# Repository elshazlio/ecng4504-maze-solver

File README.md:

# ECNG 4504 — Autonomous maze-learning & maze-solving robot

**American University in Cairo · School of Sciences and Engineering**  
**ECNG 4504 — Embedded Systems for Wireless Communications · Spring 2026**

---

## Abstract

This project is an **autonomous line-following robot** that **learns** an unknown maze in a training pass and later **executes a shortened turn sequence** to reach the goal efficiently. A **PC host** connects over **Bluetooth** (BLE with HM-10, or **Bluetooth Classic SPP** with a ZS-040 / HC-05) to issue commands, stream status, and visualize behavior. On-robot software is a single Arduino sketch (`working_code.ino`) built around **discrete line following** (no PID), **left-hand-rule** decisions at intersections, **in-place path simplification**, and **EEPROM** persistence of the optimized path.

---

## How we approached the project

We treated the work as a loop of **measure → interpret → act → log**, repeated until the vehicle behaved reliably on real tape and real junction geometry.

1. **Hardware and sensing**  
   We brought up **five reflective sensors** (left-to-right array), **differential drive** via motor drivers, and **wireless UART on `Serial1`** (HM-10 BLE or ZS-040 / HC-05 classic) so the laptop could see the same telemetry as USB debug.

2. **Baseline motion**  
   Before worrying about mapping, we stabilized **line following** using **fixed PWM steps** and simple rules from the sensor pattern (centered forward, soft correct near center, stronger correct when the line moves under an outer sensor). This deliberately avoids PID tuning loops in favor of predictable, repeatable motion on our course.

3. **Seeing intersections**  
   Real junctions rarely match ideal drawings: wide tape, gaps, and noise meant “all black” or “wide center” could mean different things. We added **timing and lockouts** (`NODE_LOCKOUT_MS`) so the robot did not re-trigger the same junction, and **short probe moves** with **burst sampling** across the array to classify **left / straight / right** exits when possible.

4. **Training as a path string**  
   During **training**, at each real decision node the robot applies the **left-hand rule**: prefer **L**, then **S**, then **R**. The sequence of taken turns is appended to a **raw path** (`L`, `S`, `R`, or `B` for dead-end / U-turn). **Dead ends** are detected when the line is lost for long enough and recovered with a **U-turn** and a recorded **`B`**.

5. **When geometry is ambiguous**  
   For **multi-exit** junctions, recording is **deferred** briefly: after the turn, the firmware **accumulates “witness”** from the outer sensors and **scores candidate exit masks** so the stored junction record matches what the robot actually saw after committing to a turn.

6. **Optimizing the remembered path**  
   After training, the firmware **folds** the raw path: any **middle `B`** (dead-end) with neighbors is combined using **turn angles** (90° increments) so backtracking detours collapse into a single equivalent turn. That yields the **optimal path** string used in solve mode.

7. **Solve mode**  
   In **solving**, the robot walks the **optimized** sequence: at each true decision node it executes the next character of `optimalPath`. If sensor classification and the stored path disagree, it logs a **mismatch** and falls back to the left-hand choice so the run degrades safely.

8. **Host software**  
   We built a **FastAPI** dashboard with **WebSockets** (`Bluetooth stuff/maze_dashboard/`) — **Bleak** for BLE, or **pyserial** to a paired **Bluetooth SPP** serial port on macOS — plus a small **Bun** log viewer (`Bluetooth stuff/log-viewer/`) to command `TRAIN` / `START`, watch logs, and debug link issues.

**Diagrams in this repo:** high-level software structure is in [`system_architecture.png`](system_architecture.png); the PCB is exported as [`PCB Schematic.png`](PCB Schematic.png). Team and roles are in [`team.md`](team.md).

---

## Firmware: theory and implementation

The firmware implements a **maze-learning** pipeline that is **graph-free** on the MCU: the map is a **string of turns**, not an explicit adjacency list. That matches the course emphasis on embedded constraints and clear state machines.

### Line following without PID

Line tracking uses **rule-based steering** (`followLineNoPID`): the center sensor defines “on track,” left/right pairs request **differential spins** at tuned speeds (`BASE_SPEED`, `TURN_SPEED`, `ALIGN_SPEED`, etc.). There is **no PID controller**—the design trades fine continuous control for **bounded behavior** that is easier to reason about on inconsistent surfaces. After turns, **`alignToCenterStrict`** recenters on a **center-only** pattern before moving forward.

### Junction detection and training probes

A **node candidate** is inferred from reflective patterns (`nodeCandidateNow`): e.g. **all sensors on line** (wide intersection) or **outer sensors with inner body**. After a lockout window, the robot stops and runs **`inspectAndHandleNodeTraining`**: short forward motion **samples bursts** of left/right/straight visibility to set **exit masks** (bits for L, S, R). The **left-hand rule** (`selectTurn`) chooses the physical turn. **Finish** is a sustained **all-black** region confirmed as the end box (`confirmEndBox`).

### Recording and deferred resolution

For junctions with **multiple** plausible exits, the firmware may **defer** committing the recorded mask (`finalizePendingTrainingRecord`, `RECORD_RESOLVE_MS`) so post-turn sensor **witnesses** improve which mask is stored with the segment time. **Single-exit** corridors force a turn without the same ambiguity.

### Path optimization (dead-end folding)

The **raw** training path includes detours. **`buildOptimalPath`** repeatedly replaces triples where the **middle turn is `B`** by summing **turn angles** (L = 270°, S = 0°, R = 90°, B = 180°) and mapping the result back to a single letter. This removes redundant **out-and-back** structure while preserving net heading.

### Solving

**Solve** mode (`inspectAndHandleNodeSolving`) indexes **`optimalPath`** with `solveStepIndex`. Only at **true** decision nodes (multiple exits, or zero exits) does it consume the next stored turn; **forced** corridors follow the obvious exit. EEPROM (`EepromMazeData`) can persist raw and optimized paths across power cycles (`LOAD`, `CLEAR`, auto-load on boot).

### Commands and telemetry

**USB and wireless UART** share the same command set (`TRAIN`, `START`/`SOLVE`, `STATUS`, `DUMP`, `LOAD`, `CLEAR`, `STOP`). Status lines (`STATE`, `STAGE`, paths, node logs) go to both streams for the dashboard and debugging.

---

## Repository contents

| Deliverable | Location |
|-------------|----------|
| MCU firmware (final) | [`working_code.ino`](working_code.ino) |
| Backend (FastAPI, BLE, WebSockets) | [`Bluetooth stuff/maze_dashboard/`](Bluetooth%20stuff/maze_dashboard/) |
| Web UI (log viewer) | [`Bluetooth stuff/log-viewer/`](Bluetooth%20stuff/log-viewer/) |
| BLE helper scripts | [`Bluetooth stuff/ble_log_receiver.py`](Bluetooth%20stuff/ble_log_receiver.py), [`Bluetooth stuff/ble_scan.py`](Bluetooth%20stuff/ble_scan.py), [`Bluetooth stuff/requirements.txt`](Bluetooth%20stuff/requirements.txt) |
| Bill of materials | [`component_list(1).xlsx`](component_list%281%29.xlsx) |
| Software architecture diagram | [`system_architecture.png`](system_architecture.png) |
| PCB schematic (image export) | [`PCB Schematic.png`](PCB%20Schematic.png) (also under [`KiCAD Stuff/`](KiCAD%20Stuff/)) |
| KiCAD project (native) | [`KiCAD Stuff/`](KiCAD%20Stuff/) — `Embedded Project.kicad_pro`, `.kicad_sch`, `.kicad_pcb`, `.kicad_prl` |
| Team | [`team.md`](team.md) |
| 3D / mechanical design | [`3d design/`](3d%20design/) (Fusion 360 `.f3z`) |
| Local dev (env + both servers) | [`DEV-SERVERS.md`](DEV-SERVERS.md) |

**KiCAD:** open **`KiCAD Stuff/Embedded Project.kicad_pro`** in **KiCad**. Local editor folders (`.history/`, `*-backups/`, lock files) are gitignored.

---

## Running the PC applications

The host uses the **same UART protocol** as USB; the **radio path** is either **Bluetooth Classic SPP** (ZS-040 / HC-05) or **BLE** (HM-10 / Nordic UART). Full copy-paste flows (both apps, stop commands, ports) are in **[`DEV-SERVERS.md`](DEV-SERVERS.md)**.

- **Classic SPP (`ZS-040 / HC-05`):** pair in macOS, then set `MAZE_BT_SERIAL` to the paired `/dev/cu.*` device (and `MAZE_BT_BAUD`, usually `9600`). Applies to **both** the maze dashboard and the log viewer.
- **BLE:** leave `MAZE_BT_SERIAL` unset. Point the **dashboard** at the robot with `MAZE_BLE_ADDR` (fixed address, skips scanning) or `MAZE_BLE_NAME` (scan by advertised name). The **log viewer** does **not** use `MAZE_BLE_ADDR`; it still expects `MAZE_BT_SERIAL` for Classic SPP.

**Maze dashboard (first-time venv)**

```bash
cd "Bluetooth stuff/maze_dashboard"
python3 -m venv .venv && source .venv/bin/activate && pip install -r requirements.txt
uvicorn app:app --reload --host 127.0.0.1 --port 8765
```

**ZS-040 / HC-05 on macOS (Bluetooth Classic SPP)** — pair the module in **System Settings → Bluetooth**, then pick the outgoing serial device (names vary; often under `/dev/cu.*`):

```bash
ls /dev/cu.*
export MAZE_BT_SERIAL=/dev/cu.YourModule-DevB
export MAZE_BT_BAUD=9600
cd "Bluetooth stuff/maze_dashboard"
source .venv/bin/activate
uvicorn app:app --reload --host 127.0.0.1 --port 8765
```

After a successful connection, you can use `export MAZE_BT_SERIAL=last` to reuse `bt_serial_last.json` beside `app.py`.

**Maze dashboard (BLE by address — example)**

Use when the robot is on the BLE path and you already know its address:

```bash
unset MAZE_BT_SERIAL
unset MAZE_BT_BAUD
export MAZE_BLE_ADDR=78:04:73:16:19:C7
cd "Bluetooth stuff/maze_dashboard"
source .venv/bin/activate
uvicorn app:app --reload --host 127.0.0.1 --port 8765
```

For scan-based BLE instead of a fixed address, omit `MAZE_BLE_ADDR` and optionally set `MAZE_BLE_NAME`. See `Bluetooth stuff/maze_dashboard/app.py` (module docstring) and `ble_discover.py` for UUID discovery.

**Path preview (SVG map):** The dashboard builds a **turtle-geometry** polyline from path strings and from **training/solve** turn lines in the log (`FORCED_TURN`, `SOLVE_FORCED_TURN`, `SOLVE_NODE`, etc.). The preview appends **one grid segment after the last logged turn** so the **final leg** and **forced** corridor exits show the same corners you see on the track; that step is **visualization-only** and does not change what the robot records or executes. Optional **local-only** regression tests for the map (not published on GitHub) may exist under `Bluetooth stuff/maze_dashboard/`; if you have them, run with `python -m unittest` in that folder using the project venv.

**Log viewer** (see `Bluetooth stuff/log-viewer/package.json` for scripts). This path uses `ble_log_receiver.py` and **Classic SPP only** — set `MAZE_BT_SERIAL` in the same shell.

```bash
cd "Bluetooth stuff/log-viewer"
bun install
export MAZE_BT_SERIAL=/dev/cu.YourModule-DevB
bun run serve
```

---

*Course project repository: **ecng4504-maze-solver_team_5** — maze learning and solving per the ECNG 4504 charter.*

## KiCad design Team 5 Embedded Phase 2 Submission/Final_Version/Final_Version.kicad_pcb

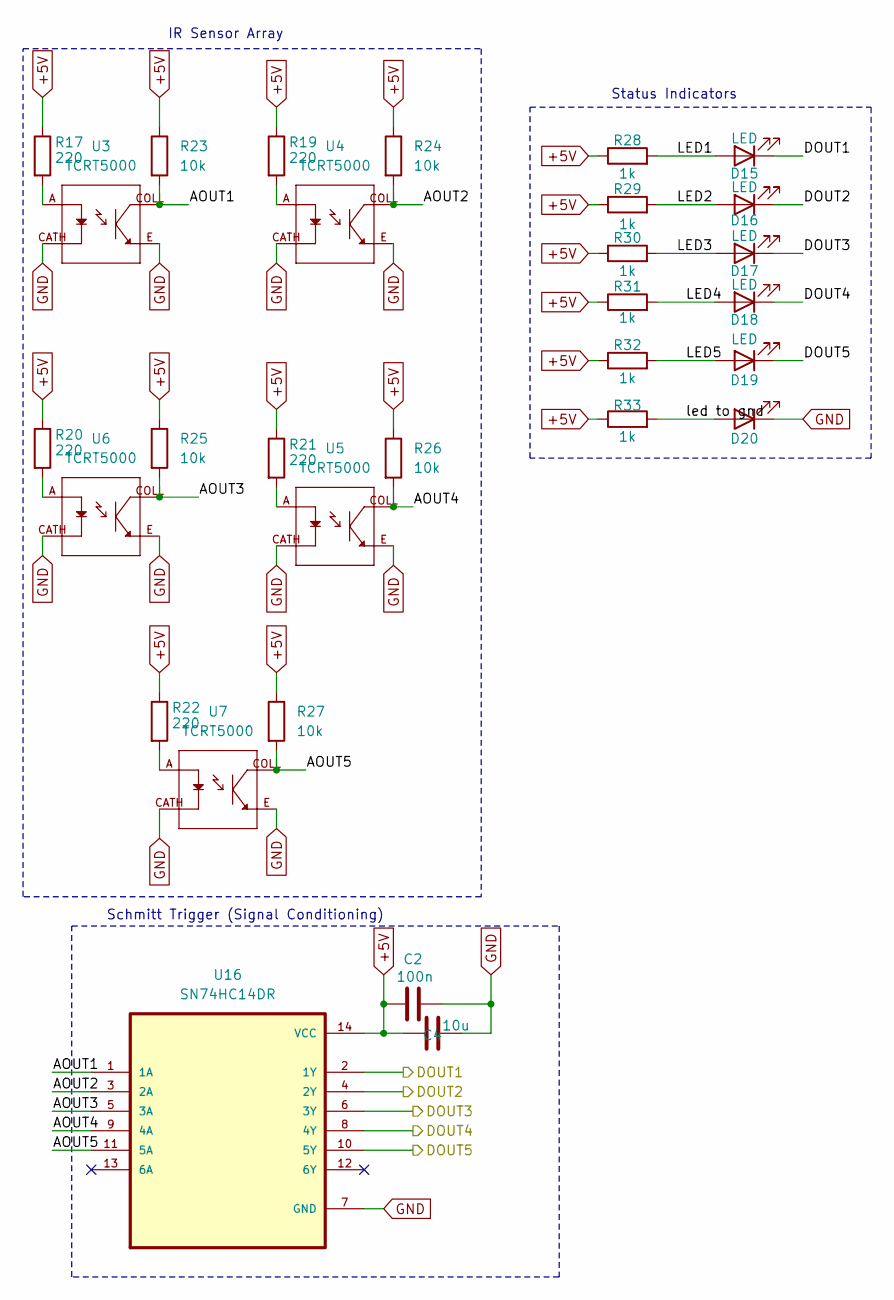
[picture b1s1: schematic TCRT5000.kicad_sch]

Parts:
C2: 100n; C_0805_2012Metric
C4: 10u; C_0805_2012Metric
D15, D16, D17, D18, D19, D20: LED; LED_0805_2012Metric
R17, R19, R20, R21, R22: 220; R_0805_2012Metric
R23, R24, R25, R26, R27: 10k; R_0805_2012Metric
R28, R29, R30, R31, R32, R33: 1k; R_0805_2012Metric
U3, U4, U5, U6, U7: TCRT5000; OPTO_TCRT5000; PARTREV 1.7
U16: SN74HC14DR; SOIC127P600X175-14N

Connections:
+5V: C2.1, C4.1, R17.1, R19.1, R20.1, R21.1, R22.1, R23.1, R24.1, R25.1, R26.1, R27.1, R28.1, R29.1, R30.1, R31.1, R32.1, R33.1, U16.14 (VCC); also elsewhere on the board
/TCRT5000/AOUT1: R23.2, U3.COLL, U16.1 (1A)
/TCRT5000/AOUT2: R24.2, U4.COLL, U16.3 (2A)
/TCRT5000/AOUT3: R25.2, U6.COLL, U16.5 (3A)
/TCRT5000/AOUT4: R26.2, U5.COLL, U16.9 (4A)
/TCRT5000/AOUT5: R27.2, U7.COLL, U16.11 (5A)
/TCRT5000/DOUT1: D15.1 (K), U16.2 (1Y); also elsewhere on the board
/TCRT5000/DOUT2: D16.1 (K), U16.4 (2Y); also elsewhere on the board
/TCRT5000/DOUT3: D17.1 (K), U16.6 (3Y); also elsewhere on the board
/TCRT5000/DOUT4: D18.1 (K), U16.8 (4Y); also elsewhere on the board
/TCRT5000/DOUT5: D19.1 (K), U16.10 (5Y); also elsewhere on the board
/TCRT5000/LED1: D15.2 (A), R28.2
/TCRT5000/LED2: D16.2 (A), R29.2
/TCRT5000/LED3: D17.2 (A), R30.2
/TCRT5000/LED4: D18.2 (A), R31.2
/TCRT5000/LED5: D19.2 (A), R32.2
/TCRT5000/led to gnd: D20.2 (A), R33.2
GND: C2.2, C4.2, D20.1 (K), U3.CATH, U3.E, U4.CATH, U4.E, U5.CATH, U5.E, U6.CATH, U6.E, U7.CATH, U7.E, U16.7 (GND); also elsewhere on the board
unnamed: R17.2, U3.A
unnamed: R19.2, U4.A
unnamed: R20.2, U6.A
unnamed: R21.2, U5.A
unnamed: R22.2, U7.A

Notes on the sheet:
IR Sensor Array
Status Indicators
Schmitt Trigger (Signal Conditioning)

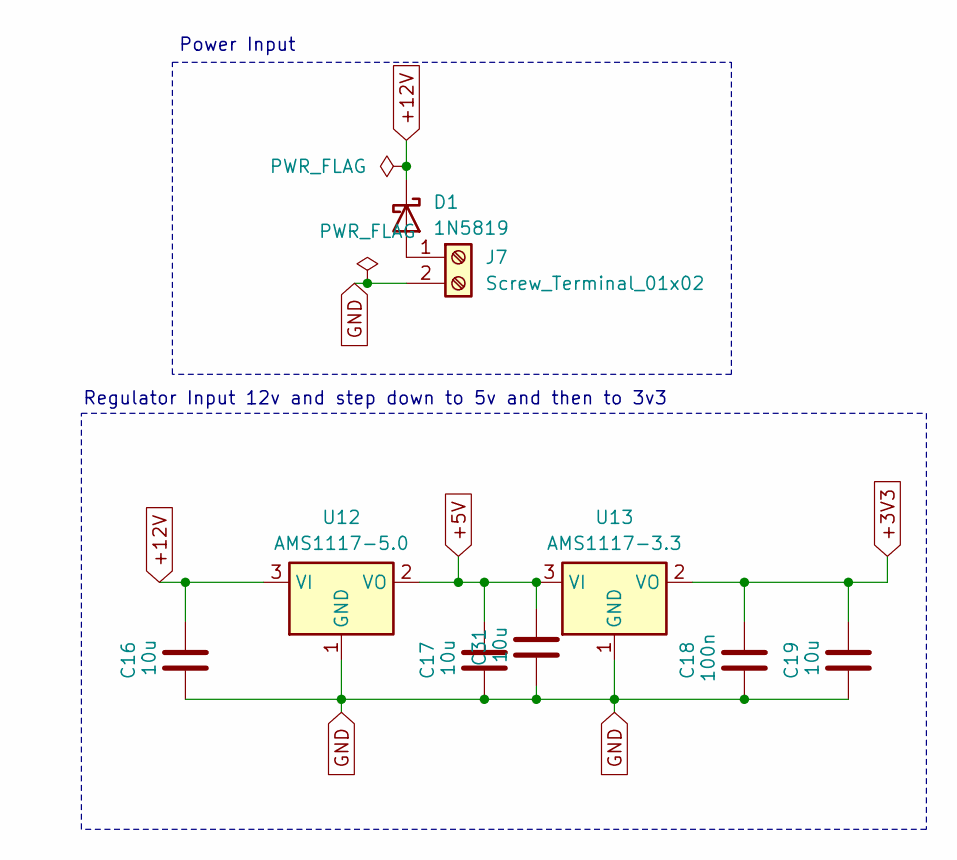
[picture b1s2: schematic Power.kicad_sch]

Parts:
C16, C17, C19, C31: 10u; C_0805_2012Metric
C18: 100n; C_0805_2012Metric
D1: 1N5819; D_SMA
J7: Screw_Terminal_01x02; TerminalBlock_Phoenix_MKDS-1,5-2-5.08_1x02_P5.08mm_Horizont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
U12: AMS1117-5.0; SOT-223-3_TabPin2
U13: AMS1117-3.3; SOT-223-3_TabPin2

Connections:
+3V3: C18.2, C19.2, U13.2 (VO); also elsewhere on the board
+5V: C17.2, C31.2, U12.2 (VO), U13.3 (VI); also elsewhere on the board
+12V: C16.2, D1.1 (K), U12.3 (VI); also elsewhere on the board
GND: C16.1, C17.1, C18.1, C19.1, C31.1, J7.2, U12.1 (GND), U13.1 (GND); also elsewhere on the board
unnamed: D1.2 (A), J7.1

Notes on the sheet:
Power Input
Regulator Input 12v and step down to 5v and then to 3v3

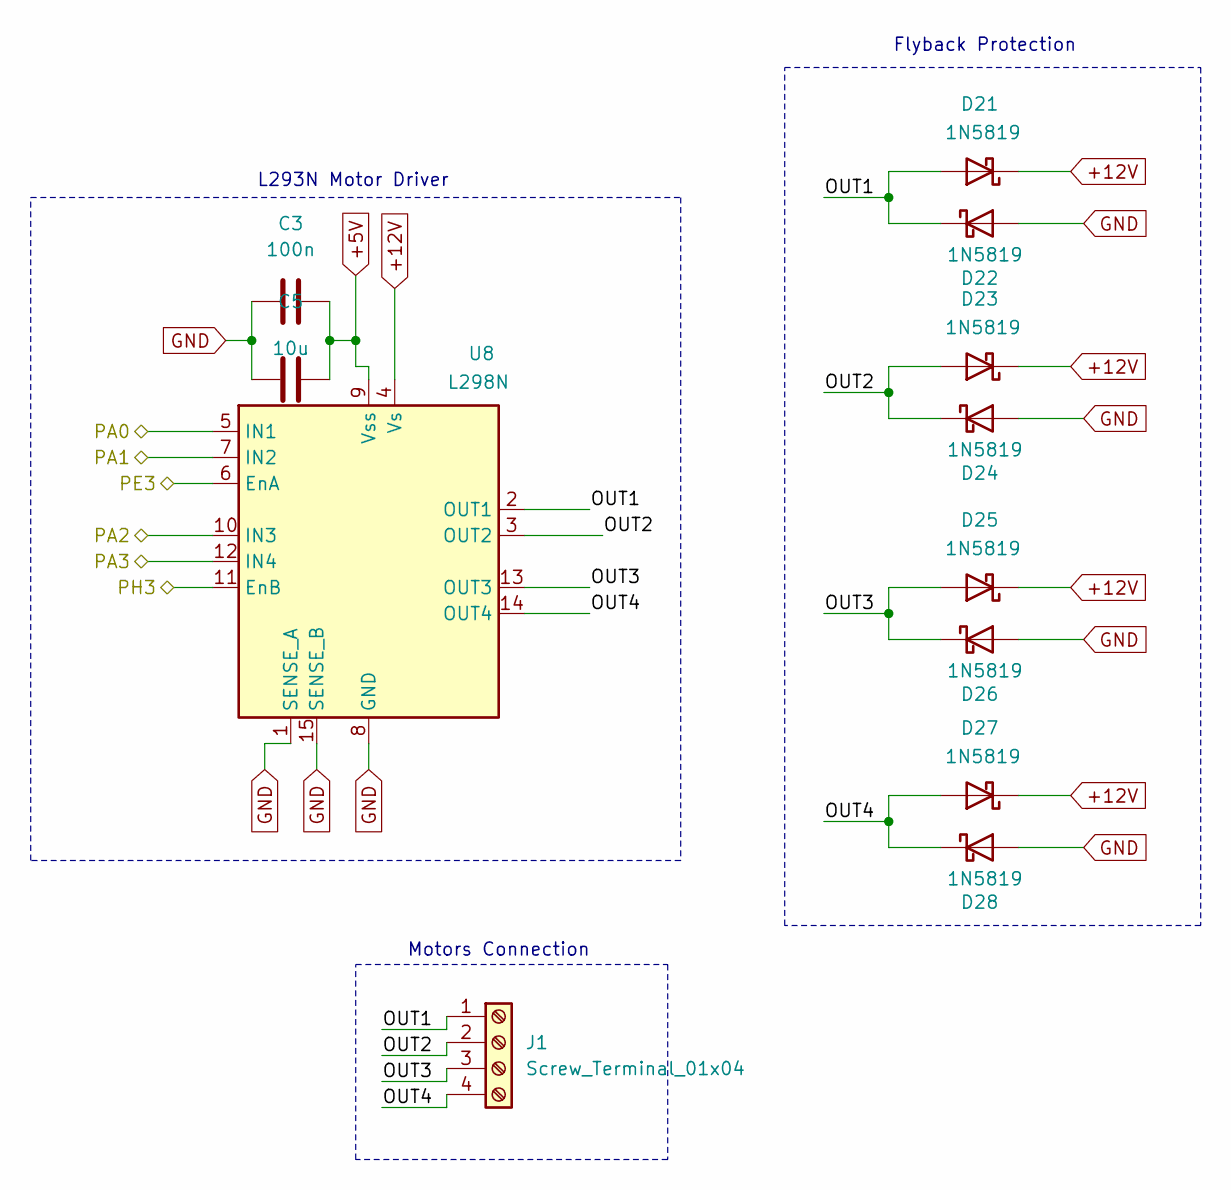
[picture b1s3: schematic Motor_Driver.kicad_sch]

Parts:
C3: 100n
C5: 10u
D21, D22, D23, D24, D25, D26, D27, D28: 1N5819; D_SMA
J1: Screw_Terminal_01x04; TerminalBlock_Phoenix_MKDS-1,5-4-5.08_1x04_P5.08mm_Horizont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
U8: L298N; TO127P2020X500X2100-15

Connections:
+5V: C3.2, C5.2, U8.9 (Vss); also elsewhere on the board
+12V: D21.1 (K), D23.1 (K), D25.1 (K), D27.1 (K), U8.4 (Vs); also elsewhere on the board
/MCU/PA0: U8.5 (IN1); also elsewhere on the board
/MCU/PA1: U8.7 (IN2); also elsewhere on the board
/MCU/PA2: U8.10 (IN3); also elsewhere on the board
/MCU/PA3: U8.12 (IN4); also elsewhere on the board
/MCU/PE3: U8.6 (EnA); also elsewhere on the board
/MCU/PH3: U8.11 (EnB); also elsewhere on the board
/Motor Driver/OUT1: D21.2 (A), D22.1 (K), J1.1, U8.2 (OUT1)
/Motor Driver/OUT2: D23.2 (A), D24.1 (K), J1.2, U8.3 (OUT2)
/Motor Driver/OUT3: D25.2 (A), D26.1 (K), J1.3, U8.13 (OUT3)
/Motor Driver/OUT4: D27.2 (A), D28.1 (K), J1.4, U8.14 (OUT4)
GND: C3.1, C5.1, D22.2 (A), D24.2 (A), D26.2 (A), D28.2 (A), U8.1 (SENSE_A), U8.8 (GND), U8.15 (SENSE_B); also elsewhere on the board

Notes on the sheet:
Flyback Protection
Motors Connection
L293N Motor Driver

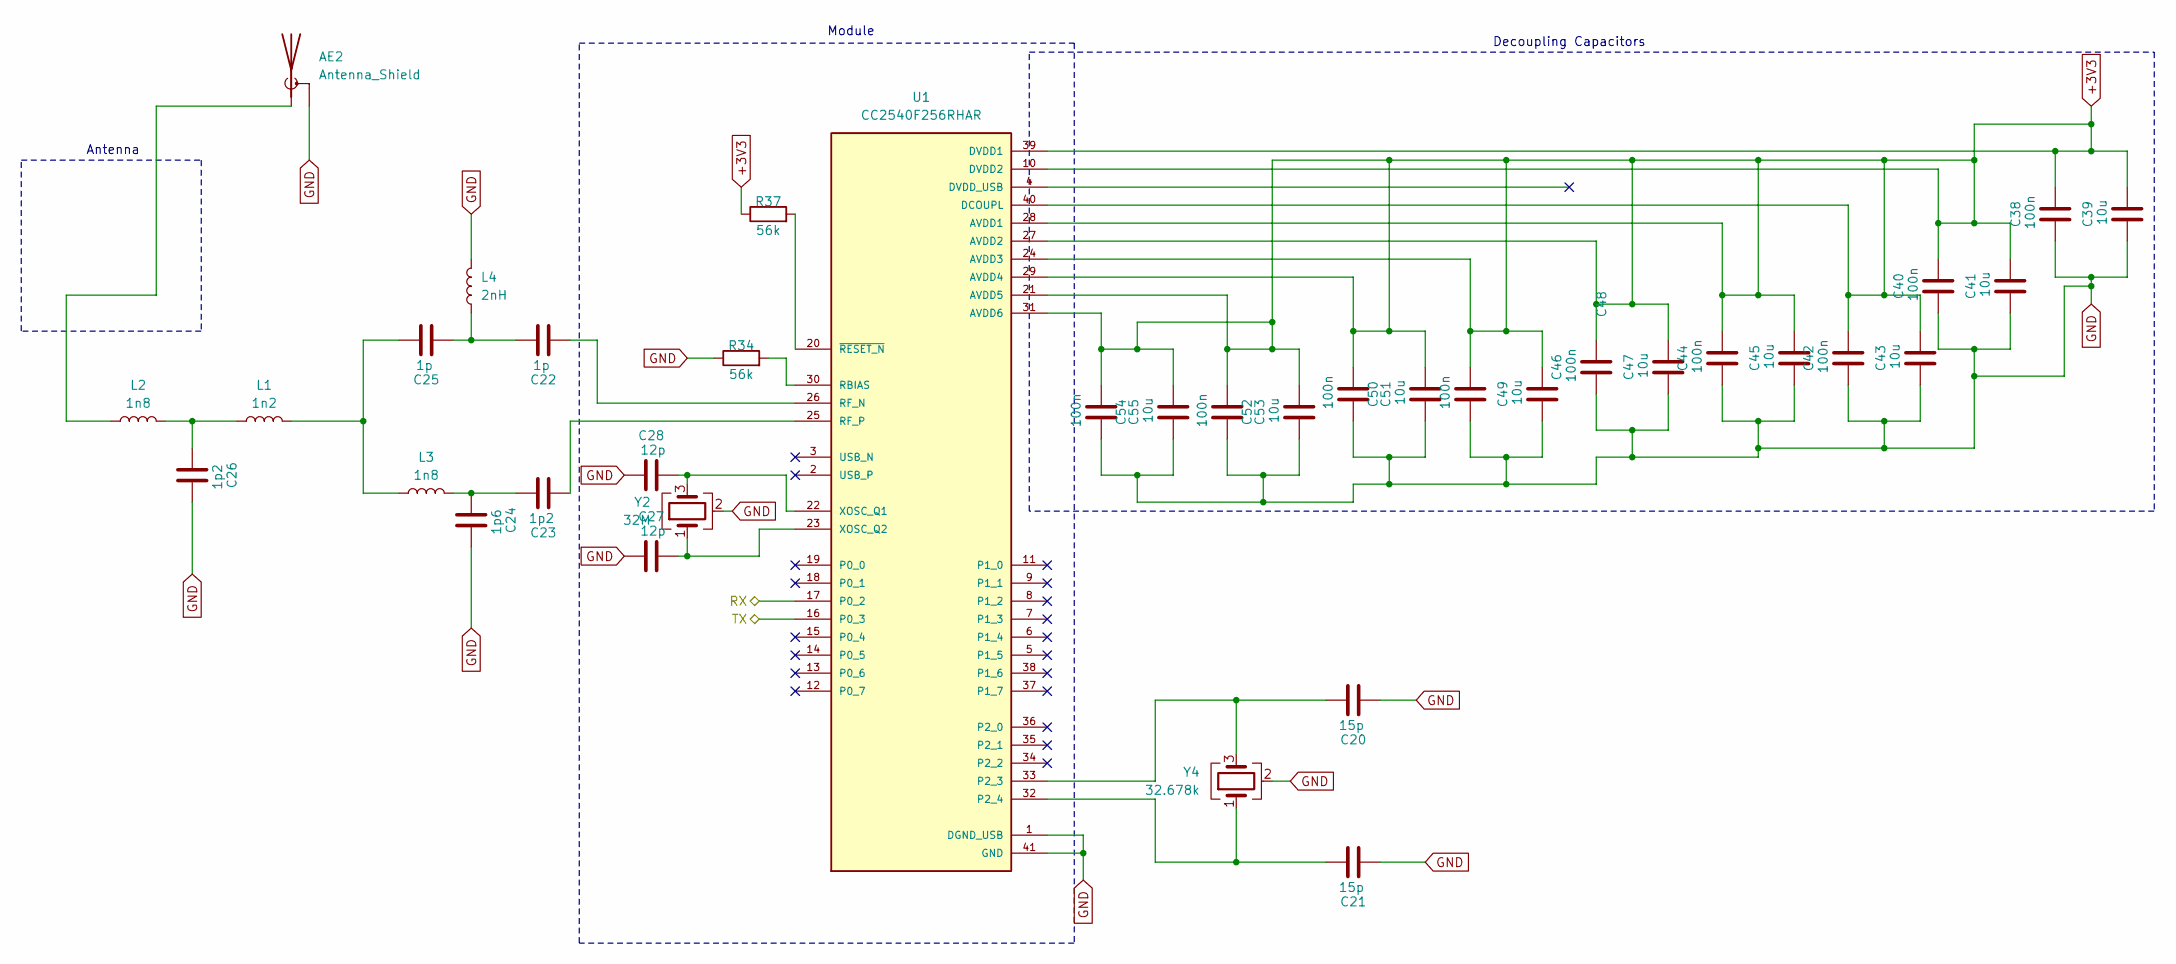
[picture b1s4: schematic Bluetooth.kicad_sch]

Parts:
AE2: Antenna_Shield; Texas_SWRA117D_2.4GHz_Right
C20, C21: 15p; C_0805_2012Metric
C22, C25: 1p; C_0805_2012Metric
C23, C26: 1p2; C_0805_2012Metric
C24: 1p6; C_0402_1005Metric
C27, C28: 12p; C_0805_2012Metric
C38, C40, C42, C44, C46, C48, C50, C52, C54: 100n; C_0805_2012Metric
C39, C41, C43, C45, C47, C49, C51, C53, C55: 10u; C_0805_2012Metric
L1: 1n2; L_0805_2012Metric
L2, L3: 1n8; L_0805_2012Metric
L4: 2nH; L_0402_1005Metric
R34, R37: 56k; R_0805_2012Metric
U1: CC2540F256RHAR; QFN50P600X600X100-41N
Y2: 32M; Crystal_SMD_3225-4Pin_3.2x2.5mm
Y4: 32.678k; Crystal_SMD_3225-4Pin_3.2x2.5mm

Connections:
+3V3: C38.2, C39.2, C40.2, C41.2, C42.2, C43.2, C44.2, C45.2, C46.2, C47.2, C48.2, C49.2, C50.2, C51.2, C52.2, C53.2, C54.2, C55.2, R37.1, U1.10 (DVDD2), U1.21 (AVDD5), U1.24 (AVDD3), U1.27 (AVDD2), U1.28 (AVDD1), U1.29 (AVDD4), U1.31 (AVDD6), U1.39 (DVDD1), U1.40 (DCOUPL); also elsewhere on the board
/Bluetooth/RX: U1.17 (P0_2); also elsewhere on the board
/Bluetooth/TX: U1.16 (P0_3); also elsewhere on the board
GND: AE2.2 (Shield), C20.1, C21.1, C24.2, C26.2, C27.1, C28.1, C38.1, C39.1, C40.1, C41.1, C42.1, C43.1, C44.1, C45.1, C46.1, C47.1, C48.1, C49.1, C50.1, C51.1, C52.1, C53.1, C54.1, C55.1, L4.2, R34.1, U1.1 (DGND_USB), U1.41 (GND), Y2.2 (G), Y2.4 (G), Y4.2 (G), Y4.4 (G); also elsewhere on the board
unnamed: AE2.1 (A), L2.1
unnamed: C22.2, C25.1, L4.1
unnamed: C23.2, C24.1, L3.2
unnamed: C25.2, L1.2, L3.1
unnamed: C26.1, L1.1, L2.2
unnamed: C20.2, U1.33 (P2_3), Y4.3
unnamed: C21.2, U1.32 (P2_4), Y4.1
unnamed: R34.2, U1.30 (RBIAS)
unnamed: C22.1, U1.26 (RF_N)
unnamed: C23.1, U1.25 (RF_P)
unnamed: C28.2, U1.22 (XOSC_Q1), Y2.3
unnamed: C27.2, U1.23 (XOSC_Q2), Y2.1
unnamed: R37.2, U1.20 (~RESET_N)

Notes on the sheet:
Module
Antenna
Decoupling Capacitors

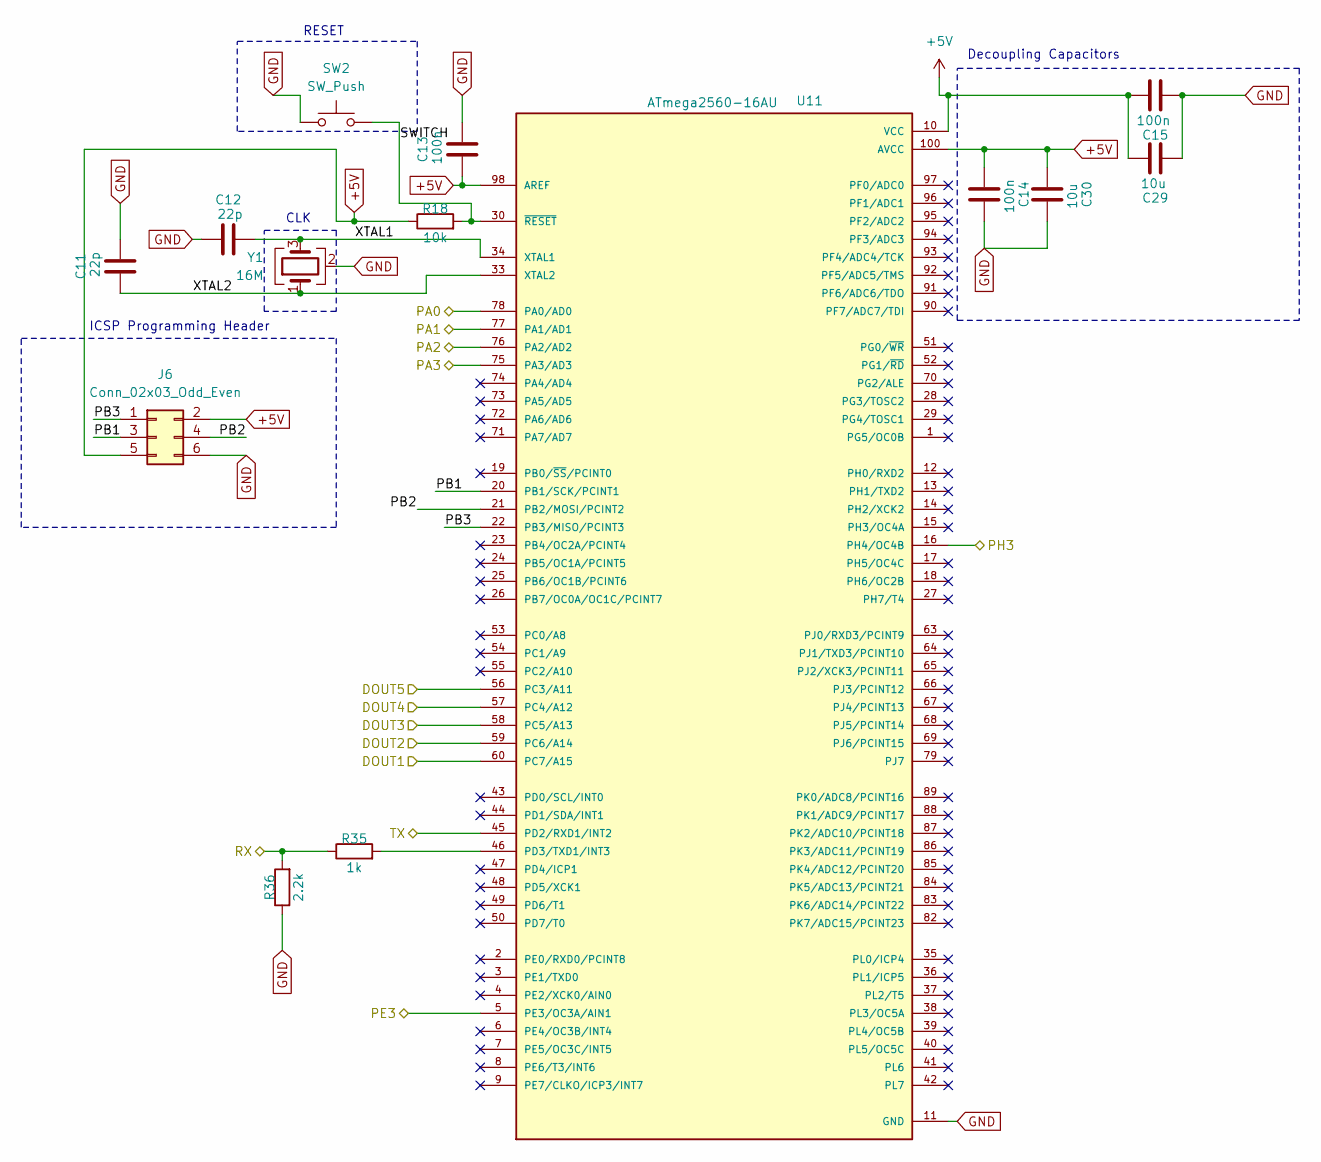
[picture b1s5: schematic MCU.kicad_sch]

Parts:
C11, C12: 22p; C_0805_2012Metric
C13, C14, C15: 100n; C_0805_2012Metric
C29, C30: 10u; C_0805_2012Metric
J6: Conn_02x03_Odd_Even; PinHeader_2x03_P2.54mm_Vertical
R18: 10k; R_0805_2012Metric
R35: 1k; R_0805_2012Metric
R36: 2.2k; R_0805_2012Metric
SW2: SW_Push; SW_SPST_PTS645Sx43SMTR92
U11: ATmega2560-16AU; QFP50P1600X1600X120-100N; PARTREV DS40002211A-05/2020
Y1: 16M

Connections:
+5V: C13.1, C14.1, C15.2, C29.2, C30.1, J6.2, J6.5, R18.1, U11.10 (VCC), U11.31 (VCC), U11.61 (VCC), U11.80 (VCC), U11.98 (AREF), U11.100 (AVCC); also elsewhere on the board
/Bluetooth/RX: R35.1, R36.2; also elsewhere on the board
/Bluetooth/TX: U11.45 (PD2/RXD1/INT2); also elsewhere on the board
/MCU/PA0: U11.78 (PA0/AD0); also elsewhere on the board
/MCU/PA1: U11.77 (PA1/AD1); also elsewhere on the board
/MCU/PA2: U11.76 (PA2/AD2); also elsewhere on the board
/MCU/PA3: U11.75 (PA3/AD3); also elsewhere on the board
/MCU/PB1: J6.3, U11.20 (PB1/SCK/PCINT1)
/MCU/PB2: J6.4, U11.21 (PB2/MOSI/PCINT2)
/MCU/PB3: J6.1, U11.22 (PB3/MISO/PCINT3)
/MCU/PE3: U11.5 (PE3/OC3A/AIN1); also elsewhere on the board
/MCU/PH3: U11.16 (PH4/OC4B); also elsewhere on the board
/MCU/SWITCH: R18.2, SW2.2, U11.30 (~RESET)
/MCU/XTAL1: C12.2, U11.34 (XTAL1), Y1.3
/MCU/XTAL2: C11.1, U11.33 (XTAL2), Y1.1
/TCRT5000/DOUT1: U11.60 (PC7/A15); also elsewhere on the board
/TCRT5000/DOUT2: U11.59 (PC6/A14); also elsewhere on the board
/TCRT5000/DOUT3: U11.58 (PC5/A13); also elsewhere on the board
/TCRT5000/DOUT4: U11.57 (PC4/A12); also elsewhere on the board
/TCRT5000/DOUT5: U11.56 (PC3/A11); also elsewhere on the board
GND: C11.2, C12.1, C13.2, C14.2, C15.1, C29.1, C30.2, J6.6, R36.1, SW2.1, U11.11 (GND), U11.32 (GND), U11.62 (GND), U11.81 (GND), U11.99 (GND), Y1.2 (G), Y1.4 (G); also elsewhere on the board
unnamed: R35.2, U11.46 (PD3/TXD1/INT3)

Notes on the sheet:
Decoupling Capacitors
RESET
CLK
ICSP Programming Header

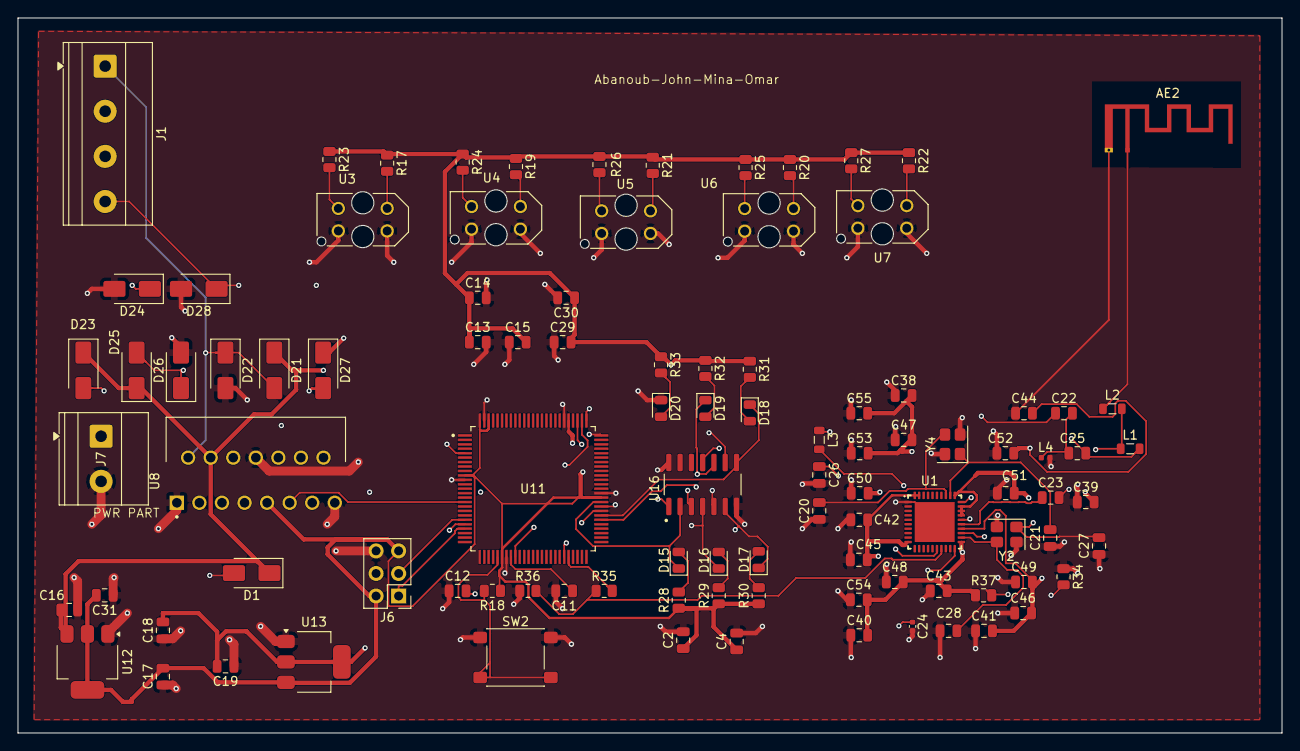
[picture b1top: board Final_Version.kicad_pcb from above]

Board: 4 copper layers, 142.3 x 80.5 mm, 99 parts (0 on the bottom side), 58 nets.

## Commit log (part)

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2026-04-16 Initial commit: ECNG 4504 monorepo (MCU, Python host, docs, diagrams)
    Single repository at project root per course GitHub deliverables: Arduino
    sketches, Bluetooth stuff/maze_dashboard Python app, log-viewer, docs including
    project charter and submission mapping.
    Made-with: Cursor
2026-04-16 Remove duplicate firmware sketch probably_final_code.ino (trashed locally)
    Made-with: Cursor
2026-04-16 chore: rename BOM to component_list.xlsx and update references
    Made-with: Cursor
2026-04-16 docs: rewrite README as project report (process and firmware theory)
    Narrate development workflow, then explain LHR mapping, no-PID line follow,
    junction probes, deferred recording, path folding, solve replay, and BLE host
    role. Keep a compact repository index and run commands.
    Made-with: Cursor
2026-04-17 Sync firmware, maze dashboard, and host tools; document path preview and SPP
    - Update working_code.ino with latest robot behavior.
    - Extend maze_dashboard (BLE/SPP, path preview polyline fix, tests).
    - Refresh ble_log_receiver, log-viewer serve, and requirements.
    - README: Bluetooth SPP setup, path preview note, unittest hint.
    - gitignore: bt_serial_last, Word lockfiles, tmp compile folders.
    Made-with: Cursor
2026-04-17 docs: expand team.md (host stack, HM-10/ZS-040, Abanoub PCB & Fusion)
    Made-with: Cursor
2026-04-17 Add KiCAD Stuff: Embedded Project sources and schematic export
    - Track .kicad_pro, .kicad_sch, .kicad_pcb, .kicad_prl, PCB Schematic.png
    - Add KiCAD Stuff/.gitignore for .history, backups, locks
    - README: table entry and KiCad open instructions
    Made-with: Cursor
2026-04-17 docs: align README Bluetooth setup with DEV-SERVERS
    Document Classic SPP vs BLE (MAZE_BLE_ADDR), link DEV-SERVERS.md,
    and clarify log viewer uses MAZE_BT_SERIAL only.
    Made-with: Cursor
2026-04-18 fix(dashboard): draw full training geometry (forced + intersection turns)
    RAW_PATH from the firmware only contains intersection turns, so after
    TRAINING_COMPLETE the SVG map dropped every forced corridor exit. Stop
    clearing training_geo_path when RAW_PATH arrives and draw it as the raw
    polyline so forced and intersection turns both appear on the track view.
    Made-with: Cursor
